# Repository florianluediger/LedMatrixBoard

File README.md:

# Led Matrix Board
This is the board layout for a circuit containing two 8x8 LED matrices controlled by some MAX7219 drivers and an ESP8266 microcontroller. It is also possible to cascade multiple boards to get a wider display.

# Required parts
 - [ESP2866 development board](https://www.gearbest.com/transmitters-receivers-module/pp_366523.html?wid=21)
 - [2x MAX27XX LED drivers](https://www.maximintegrated.com/en/products/power/display-power-control/MAX7221.html)
 - [2x 8x8 single color 60.2mm LED matrices with row cathodes and column anodes](https://www.tme.eu/de/details/lmd23088aag-101a/led-matrix-displays/wenrun/lmd23088aag-101a-01/)
 - 2x 10kOhm resistors
 - 1x 200nF ceramic capacitor
 - 1x 4.4uF electrolytic capacitor
 - a power jack
 - some sockets and headers

# Images

# Additional information
 - http://playground.arduino.cc/Main/LEDMatrix

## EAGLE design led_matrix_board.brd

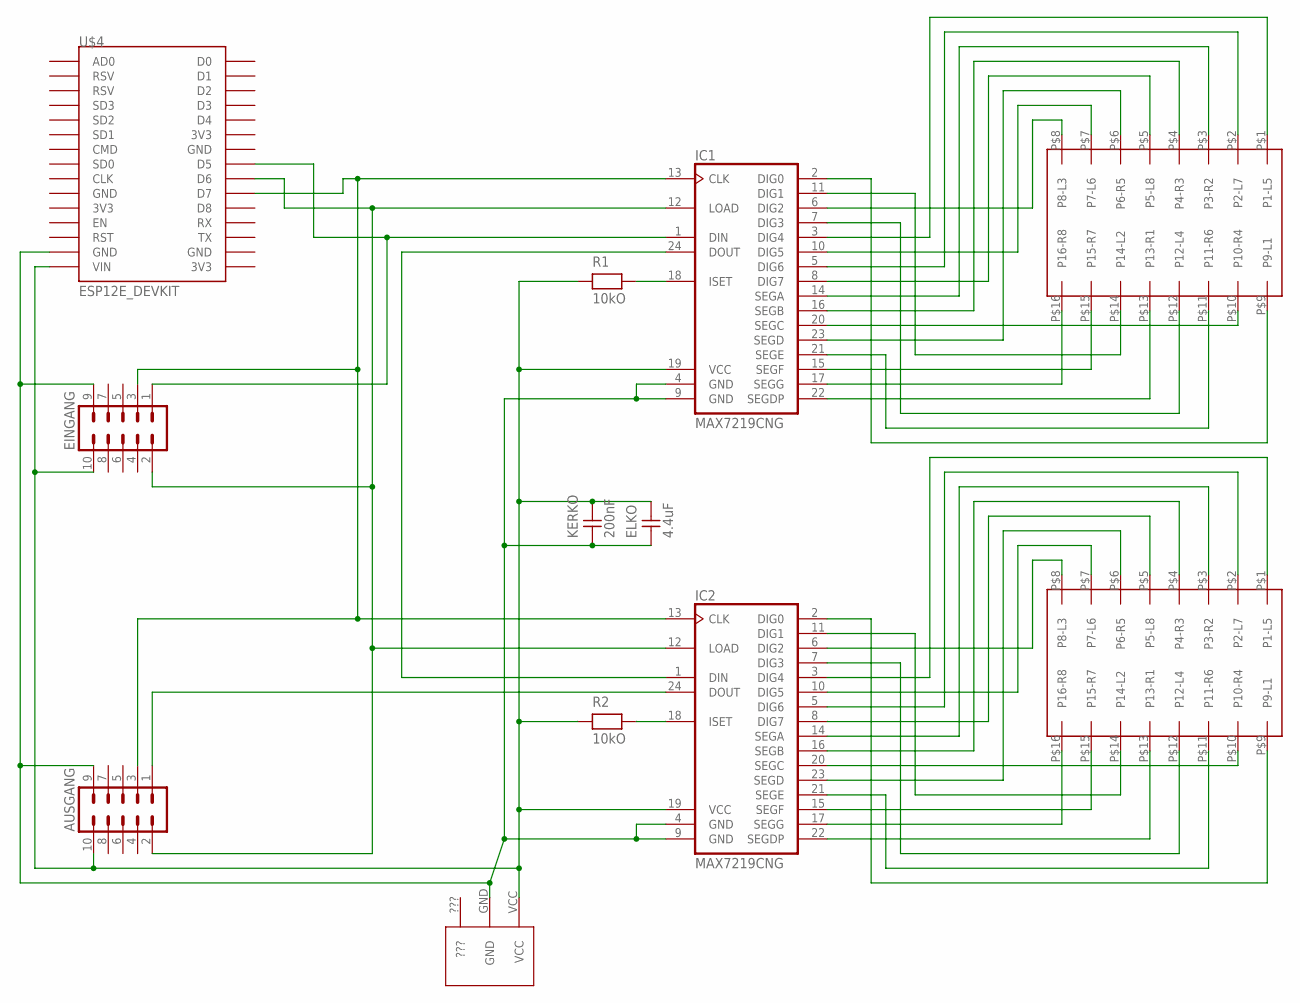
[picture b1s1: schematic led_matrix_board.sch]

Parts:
AUSGANG: ML10
EINGANG: ML10
ELKO: 4.4uF; C-5
IC1, IC2: MAX7219CNG; DIL24-3
KERKO: 200nF; C-5
R1, R2: 10kO; R-5
U$1, U$2: MATRIX
U$3: LUM1613-18; LUM16113-18
U$4: ESP12E_DEVKIT

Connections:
???: U$3.???
unnamed: IC1.20 (SEGC), U$1.P$10 (P10-R4)
unnamed: IC1.21 (SEGE), U$1.P$11 (P11-R6)
unnamed: IC2.22 (SEGDP), U$2.P$13 (P13-R1)
unnamed: IC2.14 (SEGA), U$2.P$3 (P3-R2)
unnamed: IC2.16 (SEGB), U$2.P$4 (P4-R3)
unnamed: IC2.23 (SEGD), U$2.P$6 (P6-R5)
unnamed: IC1.11 (DIG1), U$1.P$14 (P14-L2)
unnamed: IC2.15 (SEGF), U$2.P$15 (P15-R7)
unnamed: IC1.22 (SEGDP), U$1.P$13 (P13-R1)
unnamed: IC1.6 (DIG2), U$1.P$8 (P8-L3)
unnamed: IC1.7 (DIG3), U$1.P$12 (P12-L4)
unnamed: IC1.14 (SEGA), U$1.P$3 (P3-R2)
unnamed: IC1.16 (SEGB), U$1.P$4 (P4-R3)
unnamed: IC1.2 (DIG0), U$1.P$9 (P9-L1)
unnamed: IC1.23 (SEGD), U$1.P$6 (P6-R5)
unnamed: IC2.17 (SEGG), U$2.P$16 (P16-R8)
unnamed: IC1.15 (SEGF), U$1.P$15 (P15-R7)
unnamed: IC1.17 (SEGG), U$1.P$16 (P16-R8)
unnamed: IC1.3 (DIG4), U$1.P$1 (P1-L5)
unnamed: IC1.10 (DIG5), U$1.P$7 (P7-L6)
unnamed: IC2.11 (DIG1), U$2.P$14 (P14-L2)
unnamed: IC1.5 (DIG6), U$1.P$2 (P2-L7)
unnamed: IC1.8 (DIG7), U$1.P$5 (P5-L8)
unnamed: IC2.6 (DIG2), U$2.P$8 (P8-L3)
unnamed: IC2.7 (DIG3), U$2.P$12 (P12-L4)
unnamed: IC2.3 (DIG4), U$2.P$1 (P1-L5)
unnamed: IC2.10 (DIG5), U$2.P$7 (P7-L6)
unnamed: IC2.5 (DIG6), U$2.P$2 (P2-L7)
unnamed: IC2.8 (DIG7), U$2.P$5 (P5-L8)
unnamed: IC2.21 (SEGE), U$2.P$11 (P11-R6)
unnamed: IC2.20 (SEGC), U$2.P$10 (P10-R4)
unnamed: IC2.2 (DIG0), U$2.P$9 (P9-L1)
unnamed: EINGANG.1, IC1.1 (DIN), U$4.D5
unnamed: AUSGANG.3, EINGANG.3, IC1.13 (CLK), IC2.13 (CLK), U$4.D7
unnamed: IC1.24 (DOUT), IC2.1 (DIN)
unnamed: AUSGANG.2, EINGANG.2, IC1.12 (LOAD), IC2.12 (LOAD), U$4.D6
unnamed: IC1.18 (ISET), R1.2
unnamed: IC2.18 (ISET), R2.2
unnamed: AUSGANG.10, EINGANG.10, ELKO.2, IC1.19 (VCC), IC2.19 (VCC), KERKO.2, R1.1, R2.1, U$3.VCC, U$4.VIN
unnamed: AUSGANG.1, IC2.24 (DOUT)
unnamed: AUSGANG.9, EINGANG.9, ELKO.1, IC1.4 (GND), IC1.9 (GND), IC2.4 (GND), IC2.9 (GND), KERKO.1, U$3.GND, U$4.GND@1 (GND)

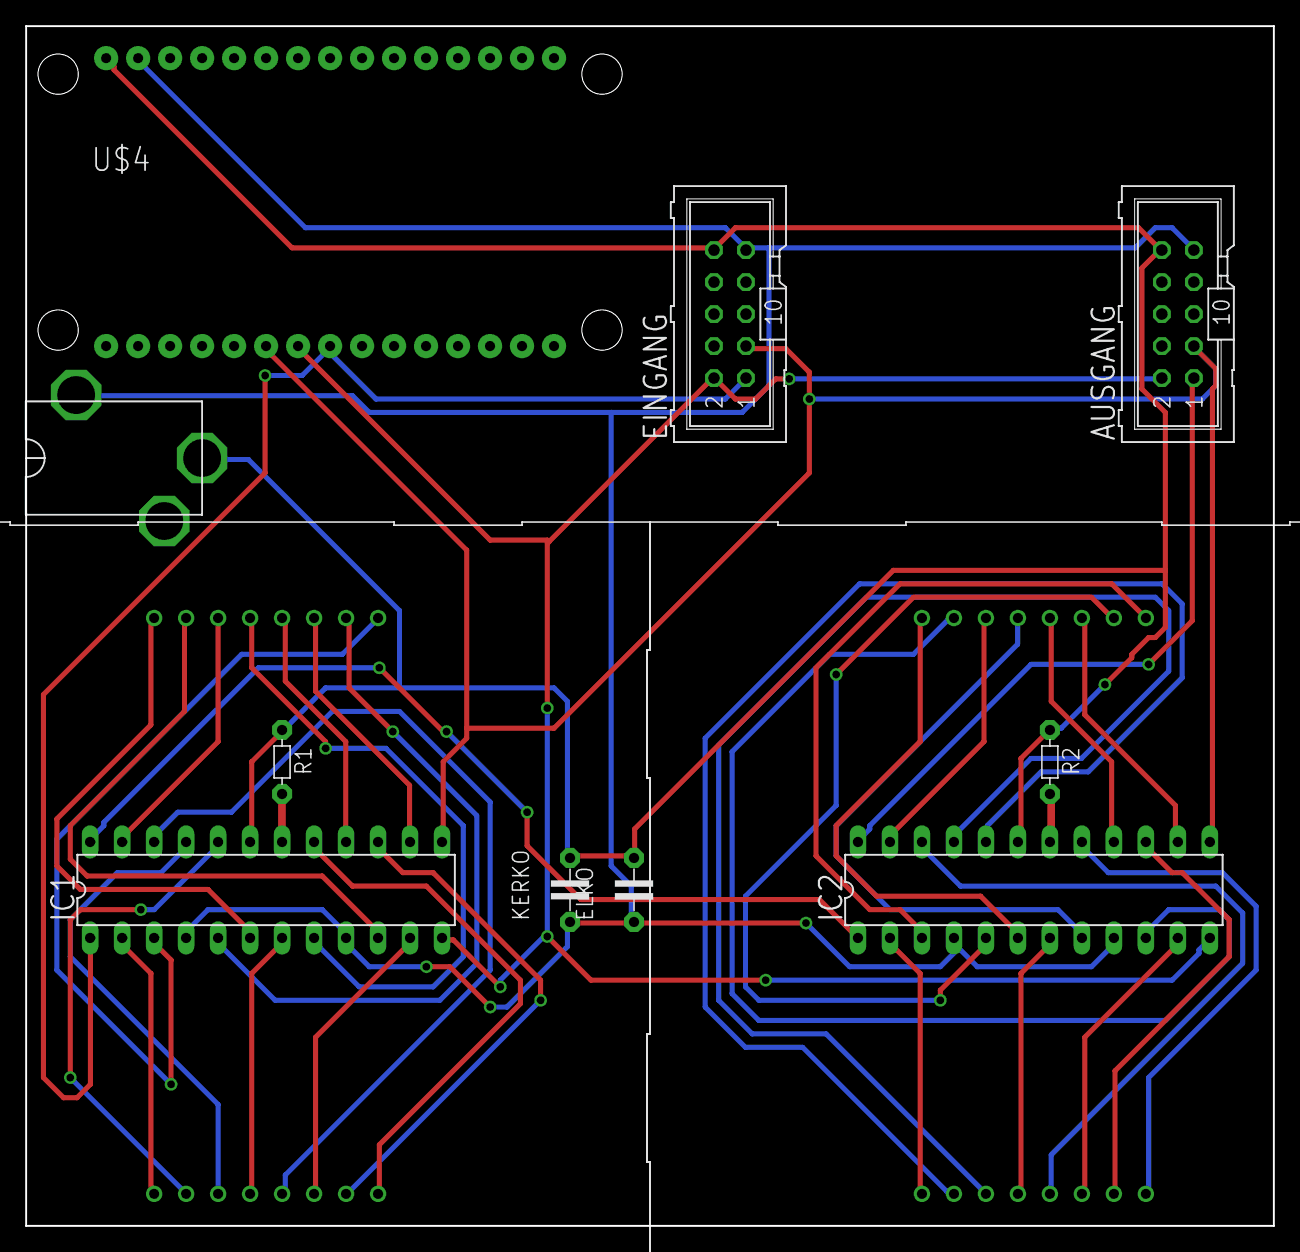
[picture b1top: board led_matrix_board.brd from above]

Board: 2 copper layers, 99.1 x 95.2 mm, 12 parts (0 on the bottom side), 41 nets.

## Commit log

2018-01-11 Import Eagle Schematic and Board
2018-01-11 Import necessary Eagle Library files
2018-01-11 Import Open Source Hardware Logo
    Use it in eagle like this:
    1. Enter command: run import-dxf
    2. Select the whole image -> Move tool -> Ctrl+Right click drag to desired
    location
    3. Select the Modify tool -> Width -> select desired width -> click on all
    the lines of the image to make them the correct thickness
2018-01-11 Add cam file to export the correct gerber files
2018-01-12 Rename Eagle files to English
2018-01-16 Add Gerber files for etching the board
2018-02-04 Add some images of the finished board
2018-02-04 Add images to the readme file
2018-02-05 Fix wrong link for the LED matrices
